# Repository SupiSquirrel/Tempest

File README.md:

# Tempest
Tempest: Etek 5 / GTek / Drone 2 / Clone 5 / Shocker SFT/NXT Paintball Board

This product is open source!

## Hardware
The hardware is released under [Creative Commons ShareAlike 4.0 International](https://creativecommons.org/licenses/by-sa/4.0/).

Please use, reuse, and modify these files as you see fit. Please release anything derivative under the same license.

Distributed as-is; no warranty is given.

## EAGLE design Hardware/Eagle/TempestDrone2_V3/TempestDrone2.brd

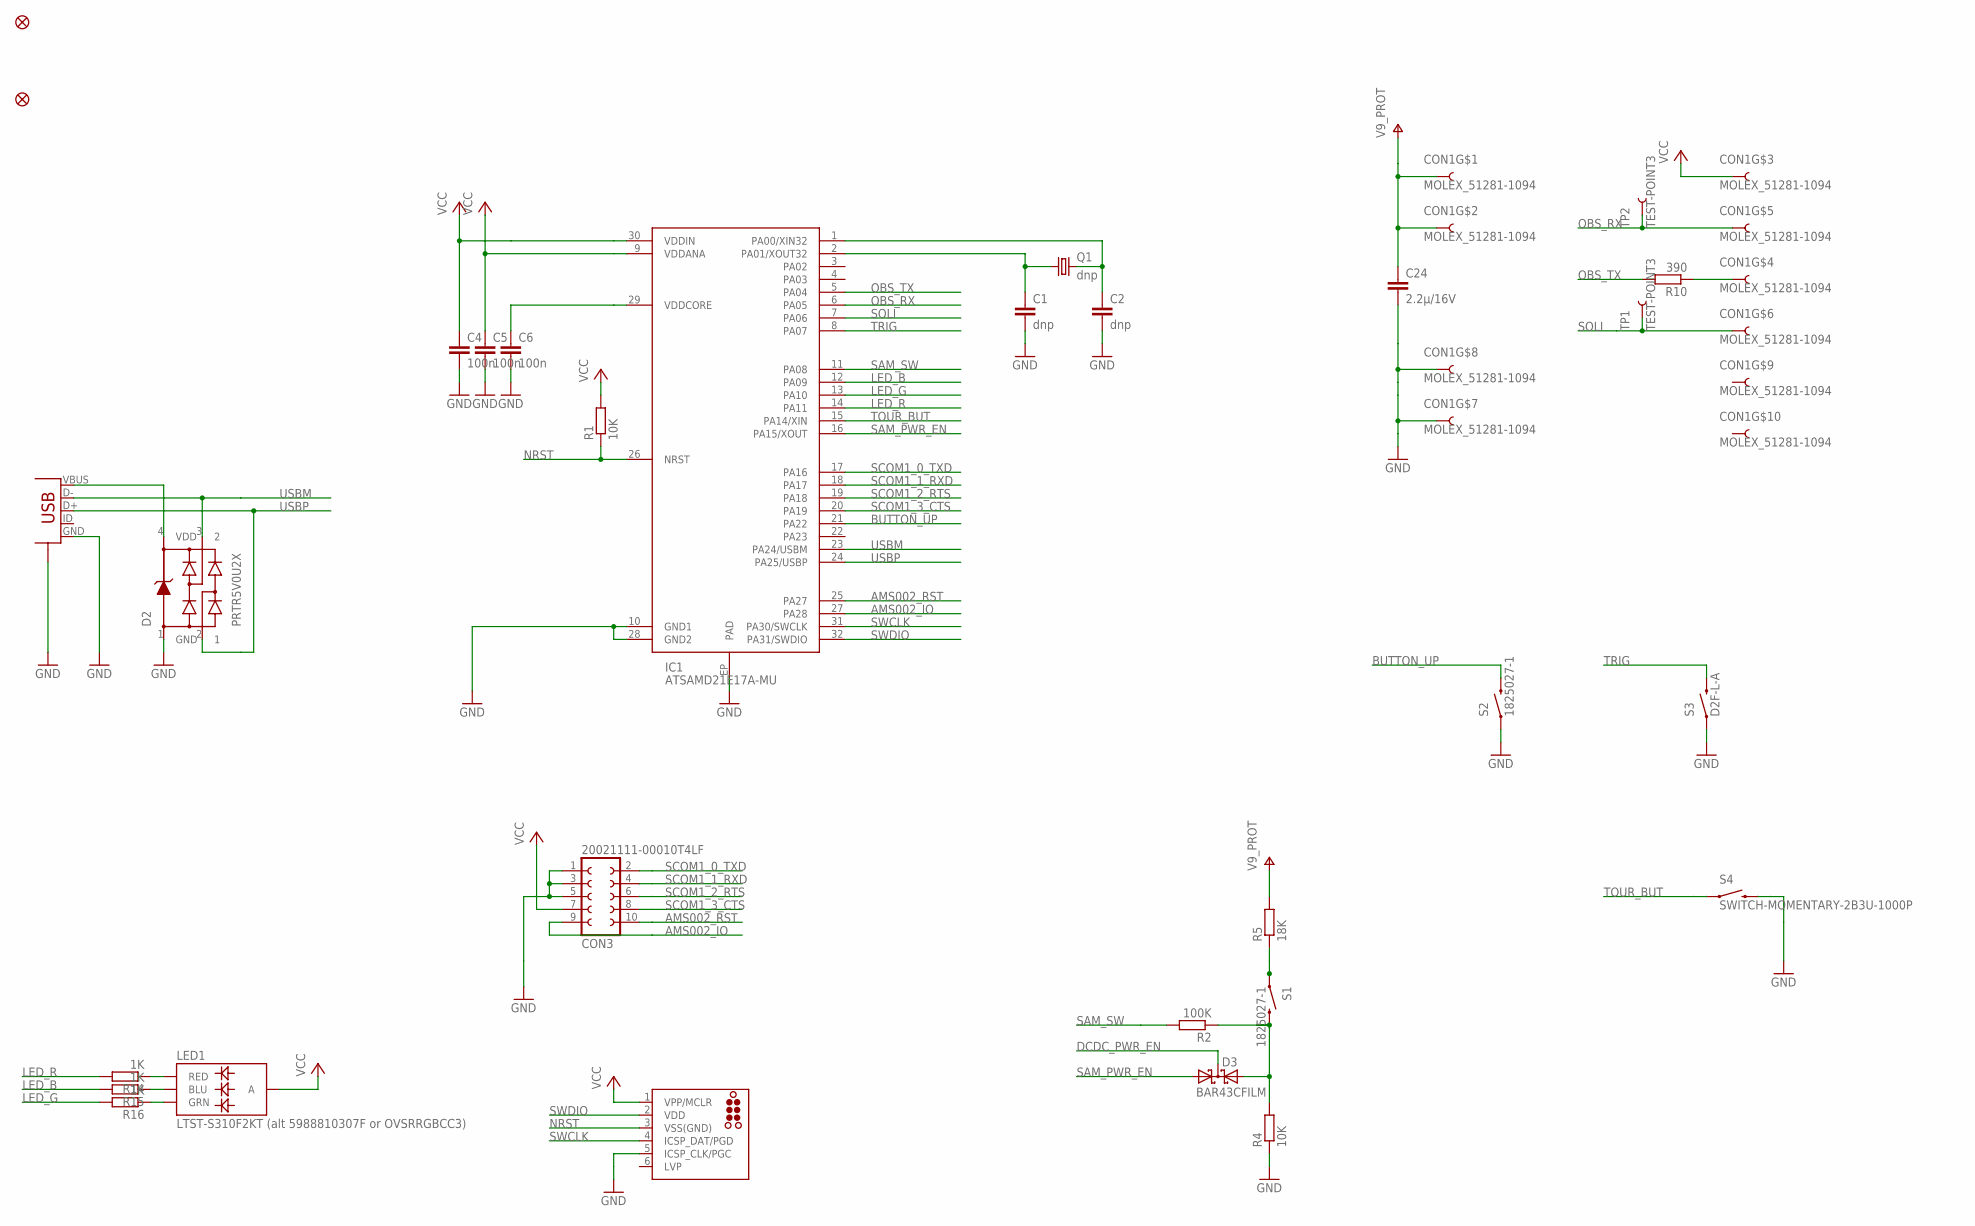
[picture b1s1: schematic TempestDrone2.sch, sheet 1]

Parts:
C1, C2: dnp; _0603MP
C4, C5, C6: 100n; _0603MP
C24: 2.2µ/16V; C0805
CON1: MOLEX_51281-1094; MOLEX_51281; PART# 51281-1094
CON3: 20021111-00010T4LF; FE02-2-HD-2; PART# 20021111-00010T4LF
CON4: USB-MICRO-A; USB-MICROB; PART# ZX62-B-5PA(11)
D2: PRTR5V0U2X; AUTOPILOT_SOT143B; PART# PRTR5V0U2X
D3: BAR43CFILM; SOT23
FID1, FID6: FIDUCIALUFIDUCIAL; MICRO-FIDUCIAL
IC1: ATSAMD21E17A-MU; QFN-32; PART# ATSAMD21E17A-MU
LED1: LTST-S310F2KT (alt 5988810307F or OVSRRGBCC3); RGB-LED-SMD-SIDE; PART# LTST-S310F2KT
Q1: dnp; XTAL_32X15
R1, R4: 10K; _0603MP
R2: 100K; _0603MP
R5: 18K; _0603MP
R10: 390; _0603MP
R14, R15, R16: 1K; _0603MP
S1, S2: 1825027-1; TACTILE-PTH-SIDEEZ; PART# 1-1825027-1
S3: D2F-L-A; D2F-A; PART# D2F-L-A
S4: SWITCH-MOMENTARY-2B3U-1000P; PUSHBUTTON-MICRO3; PART# B3U-1000P
TC2030-CTX-NL: dnp; TC2030-MCP-NL
TP1, TP2: TEST-POINT3; PAD.03X.03

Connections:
AMS002_IO: CON3.9, IC1.27 (PA28)
AMS002_RST: CON3.10, IC1.25 (PA27)
BUTTON_UP: IC1.21 (PA22), S2.2
DCDC_PWR_EN: D3.3 (CC); also elsewhere on the board
GND: C1.2, C2.2, C4.2, C5.2, C6.2, C24.2, CON1.7, CON1.8, CON3.1, CON3.3, CON3.5, CON4.GND, CON4.GND@1 (GND), CON4.GND@2 (GND), CON4.GND@3 (GND), CON4.GND@4 (GND), CON4.GND@5 (GND), CON4.GND@6 (GND), D2.1 (GND), IC1.10 (GND1), IC1.28 (GND2), IC1.EP (PAD), R4.1, S2.1, S3.COM (1), S4.2A (2), TC2030-CTX-NL.5 (ICSP_CLK/PGC); also elsewhere on the board
LED_B: IC1.12 (PA09), R15.2
LED_G: IC1.13 (PA10), R16.2
LED_R: IC1.14 (PA11), R14.2
unnamed: C2.1, IC1.1 (PA00/XIN32), Q1.2
unnamed: C6.1, IC1.29 (VDDCORE)
unnamed: C1.1, IC1.2 (PA01/XOUT32), Q1.1
unnamed: CON4.VBUS, D2.4 (VDD)
unnamed: D3.2 (A2), R2.1, R4.2, S1.2
unnamed: CON1.4, R10.1
unnamed: R5.1, S1.1
unnamed: LED1.1 (RED), R14.1
unnamed: LED1.3 (BLU), R15.1
unnamed: LED1.2 (GRN), R16.1
NRST: IC1.26 (NRST), R1.1, TC2030-CTX-NL.3 (VSS(GND))
OBS_RX: CON1.5, IC1.6 (PA05), TP2.P$1
OBS_TX: IC1.5 (PA04), R10.2
SAM_PWR_EN: D3.1 (A1), IC1.16 (PA15/XOUT)
SAM_SW: IC1.11 (PA08), R2.2
SCOM1_0_TXD: CON3.2, IC1.17 (PA16)
SCOM1_1_RXD: CON3.4, IC1.18 (PA17)
SCOM1_2_RTS: CON3.6, IC1.19 (PA18)
SCOM1_3_CTS: CON3.8, IC1.20 (PA19)
SOLI: CON1.6, IC1.7 (PA06), TP1.P$1
SWCLK: IC1.31 (PA30/SWCLK), TC2030-CTX-NL.4 (ICSP_DAT/PGD)
SWDIO: IC1.32 (PA31/SWDIO), TC2030-CTX-NL.2 (VDD)
TOUR_BUT: IC1.15 (PA14/XIN), S4.1A (1)
TRIG: IC1.8 (PA07), S3.NO (2)
USBM: CON4.D-, D2.3 (2), IC1.23 (PA24/USBM)
USBP: CON4.D+, D2.2 (1), IC1.24 (PA25/USBP)
V9_PROT: C24.1, CON1.1, CON1.2, R5.2; also elsewhere on the board
VCC: C4.1, C5.1, CON1.3, CON3.7, IC1.9 (VDDANA), IC1.30 (VDDIN), LED1.4 (A), R1.2, TC2030-CTX-NL.1 (VPP/MCLR); also elsewhere on the board

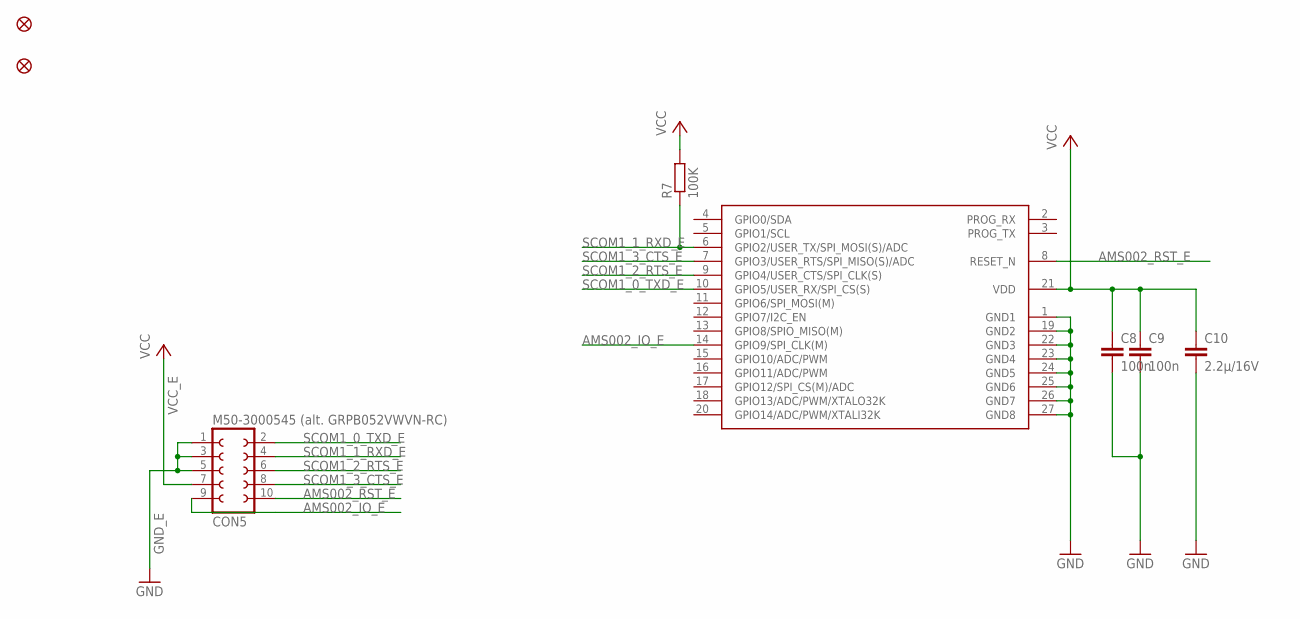
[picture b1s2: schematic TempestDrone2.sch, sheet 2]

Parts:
C8, C9: 100n; _0603MP
C10: 2.2µ/16V; C0805
CON5: M50-3000545 (alt. GRPB052VWVN-RC); FE02-2-HD-2; PART# M50-3000545
FID3, FID5: FIDUCIALUFIDUCIAL; MICRO-FIDUCIAL
R7: 100K; _0603MP
U$1: AMS001/AMS002; AMS00X; PART# AMS001 or AMS002

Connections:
AMS002_IO_E: CON5.9, U$1.14 (GPIO9/SPI_CLK(M))
AMS002_RST_E: CON5.10, U$1.8 (RESET_N)
GND_E: C8.2, C9.2, C10.2, CON5.1, CON5.3, CON5.5, U$1.1 (GND1), U$1.19 (GND2), U$1.22 (GND3), U$1.23 (GND4), U$1.24 (GND5), U$1.25 (GND6), U$1.26 (GND7), U$1.27 (GND8)
SCOM1_0_TXD_E: CON5.2, U$1.10 (GPIO5/USER_RX/SPI_CS(S))
SCOM1_1_RXD_E: CON5.4, R7.1, U$1.6 (GPIO2/USER_TX/SPI_MOSI(S)/ADC)
SCOM1_2_RTS_E: CON5.6, U$1.9 (GPIO4/USER_CTS/SPI_CLK(S))
SCOM1_3_CTS_E: CON5.8, U$1.7 (GPIO3/USER_RTS/SPI_MISO(S)/ADC)
VCC_E: C8.1, C9.1, C10.1, CON5.7, R7.2, U$1.21 (VDD)

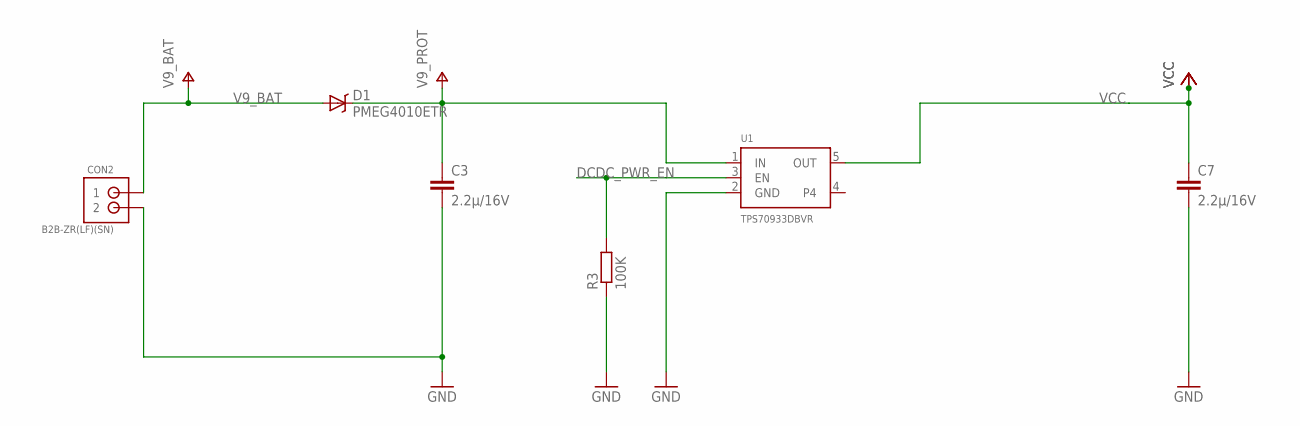
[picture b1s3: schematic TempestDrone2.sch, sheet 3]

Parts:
C3, C7: 2.2µ/16V; C0805
CON2: B2B-ZR(LF)(SN); S2B-ZR; PART# B2B-ZR(LF)(SN)
D1: PMEG4010ETR; SOD123
R3: 100K; _0603MP
U1: TPS70933DBVR; SOT23-5; PART# TPS70933DBVR

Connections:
DCDC_PWR_EN: R3.2, U1.3 (EN); also elsewhere on the board
GND: C3.2, C7.2, CON2.2, R3.1, U1.2 (GND); also elsewhere on the board
V9_BAT: CON2.1, D1.A
V9_PROT: C3.1, D1.C, U1.1 (IN); also elsewhere on the board
VCC: C7.1, U1.5 (OUT); also elsewhere on the board

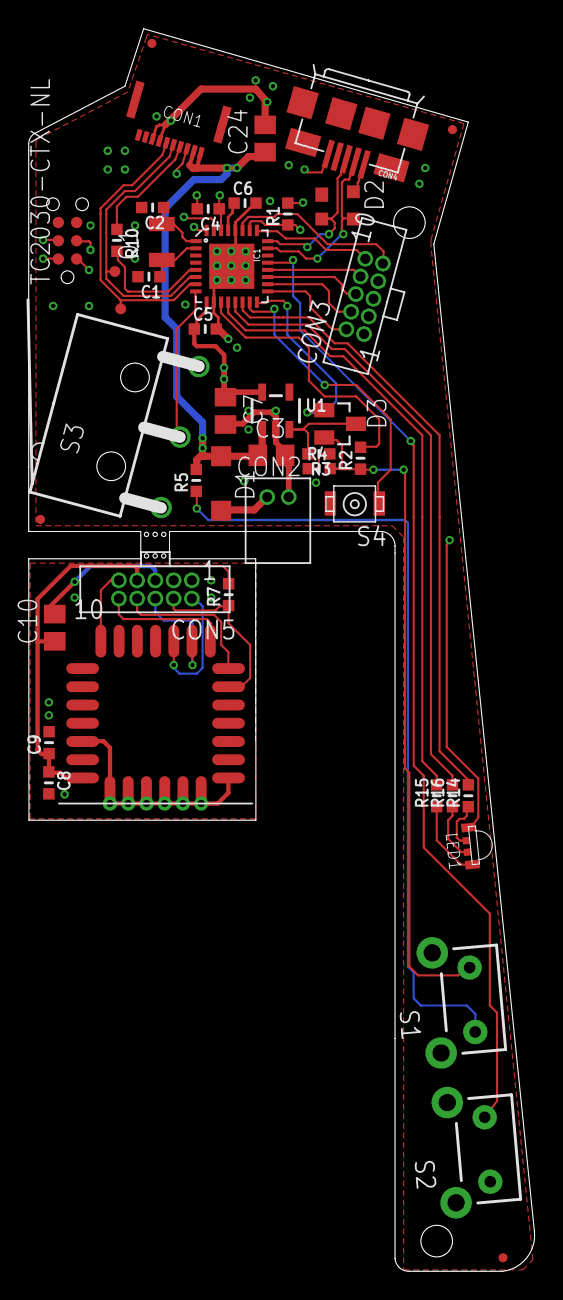
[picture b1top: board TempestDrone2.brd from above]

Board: 4 copper layers, 35.2 x 86.5 mm, 45 parts (0 on the bottom side), 45 nets.

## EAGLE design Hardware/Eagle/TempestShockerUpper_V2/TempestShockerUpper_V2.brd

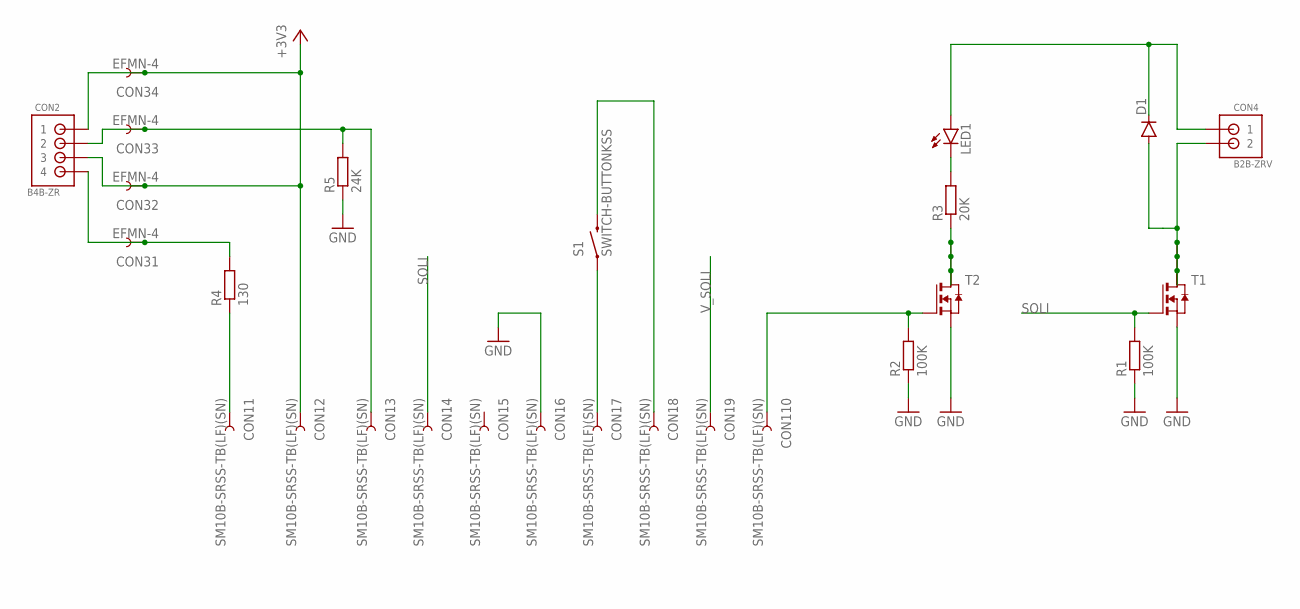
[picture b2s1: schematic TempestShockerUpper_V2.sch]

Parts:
CON1: SM10B-SRSS-TB(LF)(SN); SM10B-SRSS-TB
CON2: B4B-ZR; S4B-ZR
CON3: EFMN-4
CON4: B2B-ZRV; S2B-ZR-VERT
D1: DIODE-SSOD123; SOD-123
LED1: LED0603; LED-0603
R1, R2: 100K; _0603MP
R3: 20K; _0603MP
R4: 130; _0603MP
R5: 24K; _0603MP
S1: SWITCH-BUTTONKSS; KSS
T1, T2: NMOSSOT23-6; SOT23-6

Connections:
+3V3: CON1.2, CON2.1, CON2.3, CON3.2, CON3.4
GND: CON1.6, R1.1, R2.1, R5.1, T1.4 (S), T2.4 (S)
unnamed: CON2.4, CON3.1, R4.2
unnamed: CON1.1, R4.1
unnamed: CON1.3, CON2.2, CON3.3, R5.2
unnamed: CON1.10, R2.2, T2.3 (G)
unnamed: CON1.7, S1.1
unnamed: CON1.8, S1.2
unnamed: LED1.C, R3.2
unnamed: R3.1, T2.1 (D), T2.2 (D1), T2.5 (D2), T2.6 (D3)
unnamed: CON4.2, D1.A, T1.1 (D), T1.2 (D1), T1.5 (D2), T1.6 (D3)
SOLI: CON1.4, R1.2, T1.3 (G)
V_SOLI: CON1.9, CON4.1, D1.C, LED1.A

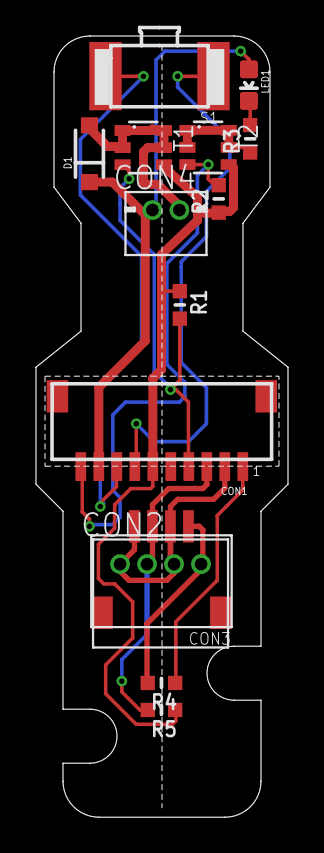
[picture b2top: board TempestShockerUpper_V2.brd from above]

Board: 2 copper layers, 14.0 x 43.4 mm, 15 parts (0 on the bottom side), 13 nets.

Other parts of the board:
U$2: SHOCKER-OUTLINE-UPPER-SHORT

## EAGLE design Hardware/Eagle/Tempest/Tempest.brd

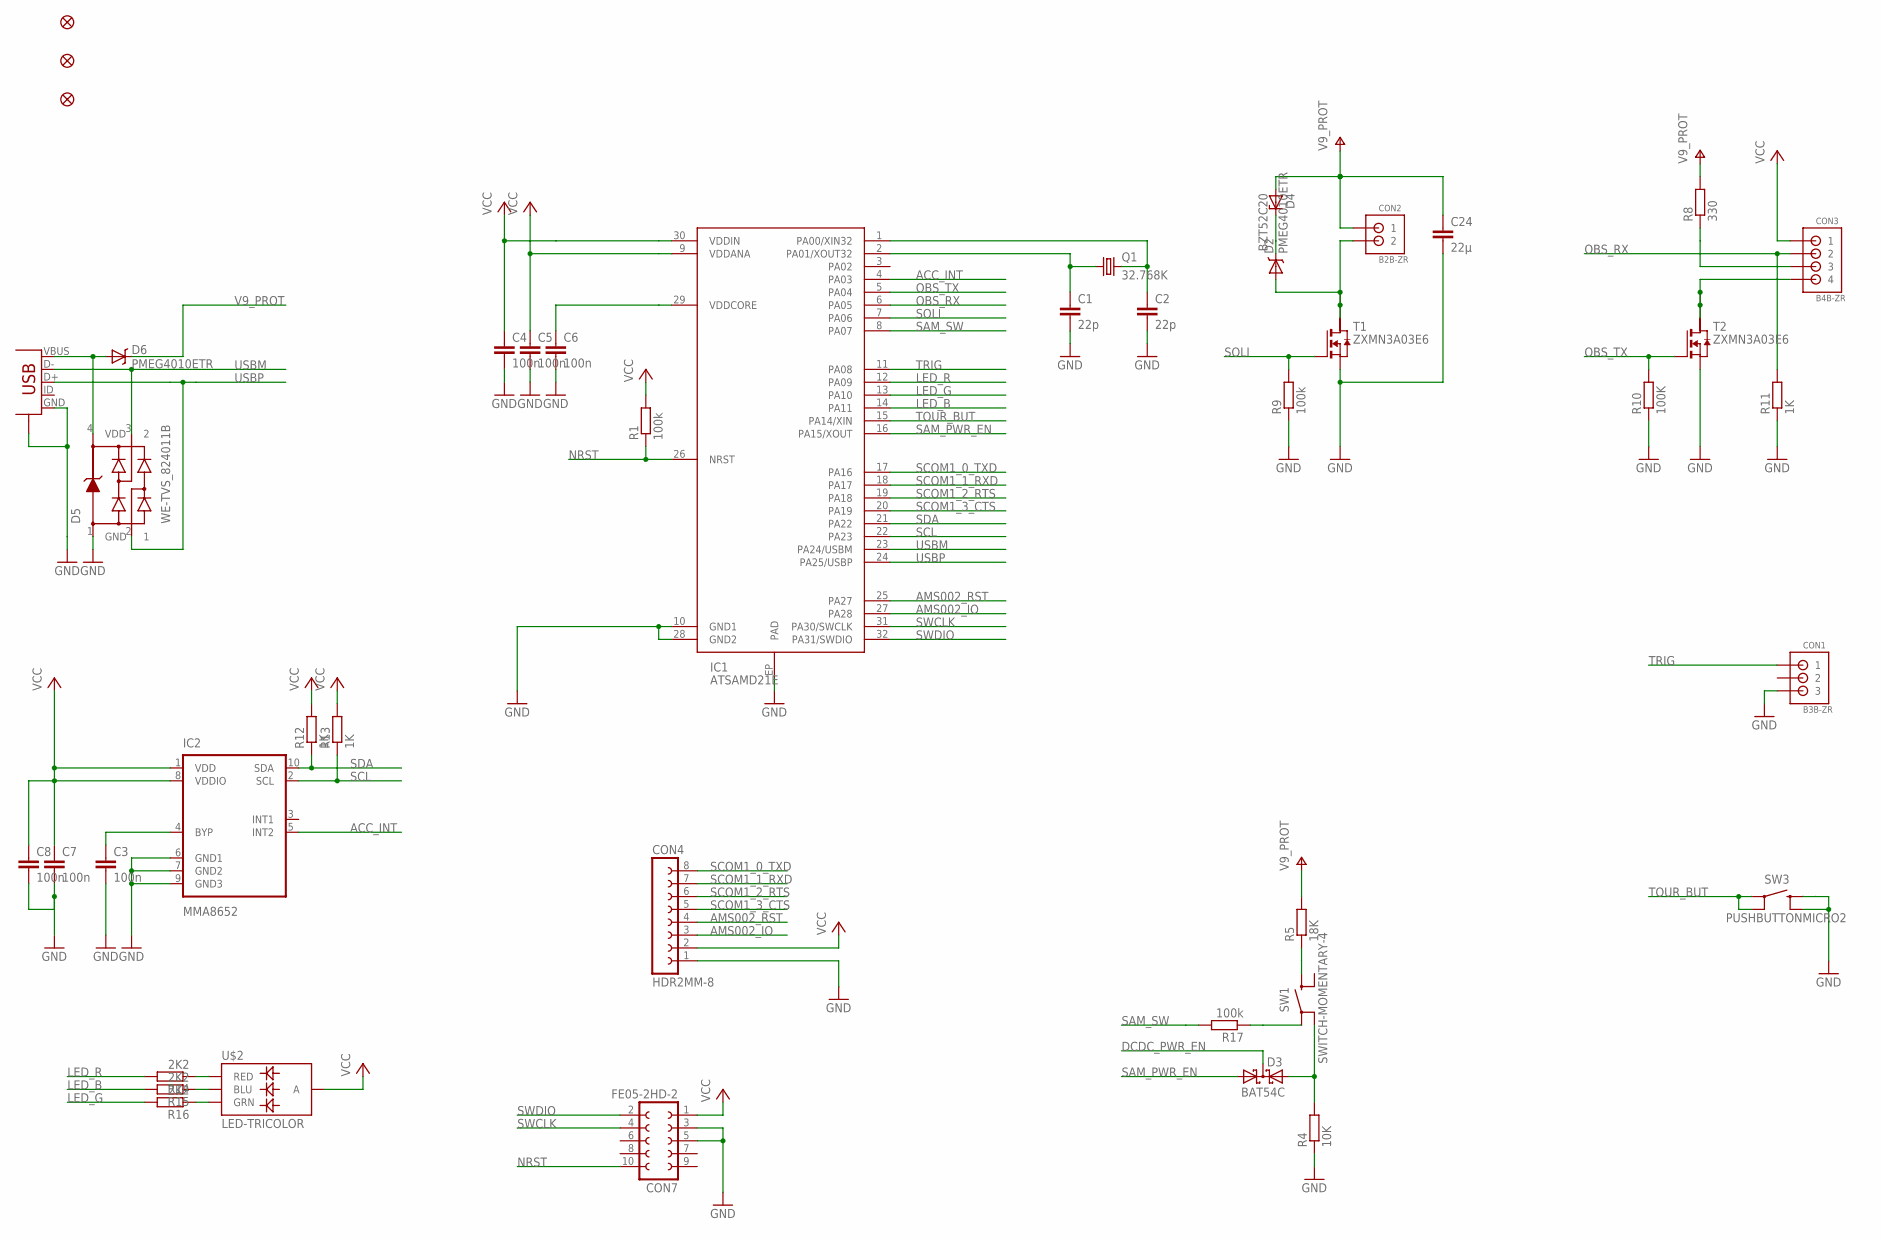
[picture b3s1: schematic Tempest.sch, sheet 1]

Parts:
C1, C2: 22p; _0603MP
C3, C4, C5, C6, C7, C8: 100n; _0603MP
C24: 22µ; C1206
CON1: B3B-ZR; S3B-ZR
CON2: B2B-ZR; S2B-ZR
CON3: B4B-ZR; S4B-ZR
CON4: HDR2MM-8
CON6: USB-MICRO-A; USB-MICROB
CON7: FE05-2HD-2; FE02-2-HD-2
D2, D6: PMEG4010ETR; SOD123
D3: BAT54C; SOT23
D4: BZT52C20; SOD123
D5: WE-TVS_824011B; AUTOPILOT_SOT143B
FID1, FID2, FID6: FIDUCIALUFIDUCIAL; MICRO-FIDUCIAL
IC1: ATSAMD21E; QFN-32
IC2: MMA8652; DFN-10
Q1: 32.768K; XTAL_32X15
R1, R9, R17: 100k; _0603MP
R4: 10K; _0603MP
R5: 18K; _0603MP
R8: 330; R0805
R10: 100K; _0603MP
R11, R12, R13: 1K; _0603MP
R14, R15, R16: 2K2; _0603MP
SW1: SWITCH-MOMENTARY-4; TACTILE_SWITCH_TALL
SW3: PUSHBUTTONMICRO2; PUSHBUTTON-MICRO2
T1, T2: ZXMN3A03E6; SOT23-6
U$2: LED-TRICOLOR; LED-TRICOLOR-SMD

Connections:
ACC_INT: IC1.4 (PA03), IC2.5 (INT2)
AMS002_IO: CON4.3, IC1.27 (PA28)
AMS002_RST: CON4.4, IC1.25 (PA27)
DCDC_PWR_EN: D3.3 (CC); also elsewhere on the board
GND: C1.2, C2.2, C3.2, C4.2, C5.2, C6.2, C7.2, C8.2, C24.2, CON1.3, CON4.1, CON6.GND, CON6.GND@1 (GND), CON6.GND@2 (GND), CON6.GND@3 (GND), CON6.GND@4 (GND), CON6.GND@5 (GND), CON6.GND@6 (GND), CON7.3, CON7.5, D5.1 (GND), IC1.10 (GND1), IC1.28 (GND2), IC1.EP (PAD), IC2.6 (GND1), IC2.7 (GND2), IC2.9 (GND3), R4.1, R9.1, R10.1, R11.1, SW3.2A (2), SW3.2B (2A), T1.4 (S), T2.4 (S); also elsewhere on the board
LED_B: IC1.14 (PA11), R15.2
LED_G: IC1.13 (PA10), R16.2
LED_R: IC1.12 (PA09), R14.2
unnamed: C2.1, IC1.1 (PA00/XIN32), Q1.2
unnamed: C6.1, IC1.29 (VDDCORE)
unnamed: C1.1, IC1.2 (PA01/XOUT32), Q1.1
unnamed: D3.2 (A2), R4.2, SW1.A2 (1A)
unnamed: CON2.2, D2.A, T1.1 (D), T1.2 (D1), T1.6 (D3)
unnamed: R5.1, SW1.B1 (2)
unnamed: R17.1, SW1.A1 (1)
unnamed: C3.1, IC2.4 (BYP)
unnamed: CON3.4, T2.1 (D), T2.2 (D1), T2.6 (D3)
unnamed: CON3.3, R8.1
unnamed: D2.C, D4.C
unnamed: CON6.VBUS, D5.4 (VDD), D6.A
unnamed: R14.1, U$2.2 (RED)
unnamed: R15.1, U$2.3 (BLU)
unnamed: R16.1, U$2.4 (GRN)
NRST: CON7.10, IC1.26 (NRST), R1.1
OBS_RX: CON3.2, IC1.6 (PA05), R11.2
OBS_TX: IC1.5 (PA04), R10.2, T2.3 (G)
SAM_PWR_EN: D3.1 (A1), IC1.16 (PA15/XOUT)
SAM_SW: IC1.8 (PA07), R17.2
SCL: IC1.22 (PA23), IC2.2 (SCL), R13.1
SCOM1_0_TXD: CON4.8, IC1.17 (PA16)
SCOM1_1_RXD: CON4.7, IC1.18 (PA17)
SCOM1_2_RTS: CON4.6, IC1.19 (PA18)
SCOM1_3_CTS: CON4.5, IC1.20 (PA19)
SDA: IC1.21 (PA22), IC2.10 (SDA), R12.1
SOLI: IC1.7 (PA06), R9.2, T1.3 (G)
SWCLK: CON7.4, IC1.31 (PA30/SWCLK)
SWDIO: CON7.2, IC1.32 (PA31/SWDIO)
TOUR_BUT: IC1.15 (PA14/XIN), SW3.1A (1), SW3.1B (1A)
TRIG: CON1.1, IC1.11 (PA08)
USBM: CON6.D-, D5.3 (2), IC1.23 (PA24/USBM)
USBP: CON6.D+, D5.2 (1), IC1.24 (PA25/USBP)
V9_PROT: C24.1, CON2.1, D4.A, D6.C, R5.2, R8.2; also elsewhere on the board
VCC: C4.1, C5.1, C7.1, C8.1, CON3.1, CON4.2, CON7.1, IC1.9 (VDDANA), IC1.30 (VDDIN), IC2.1 (VDD), IC2.8 (VDDIO), R1.2, R12.2, R13.2, U$2.1 (A); also elsewhere on the board

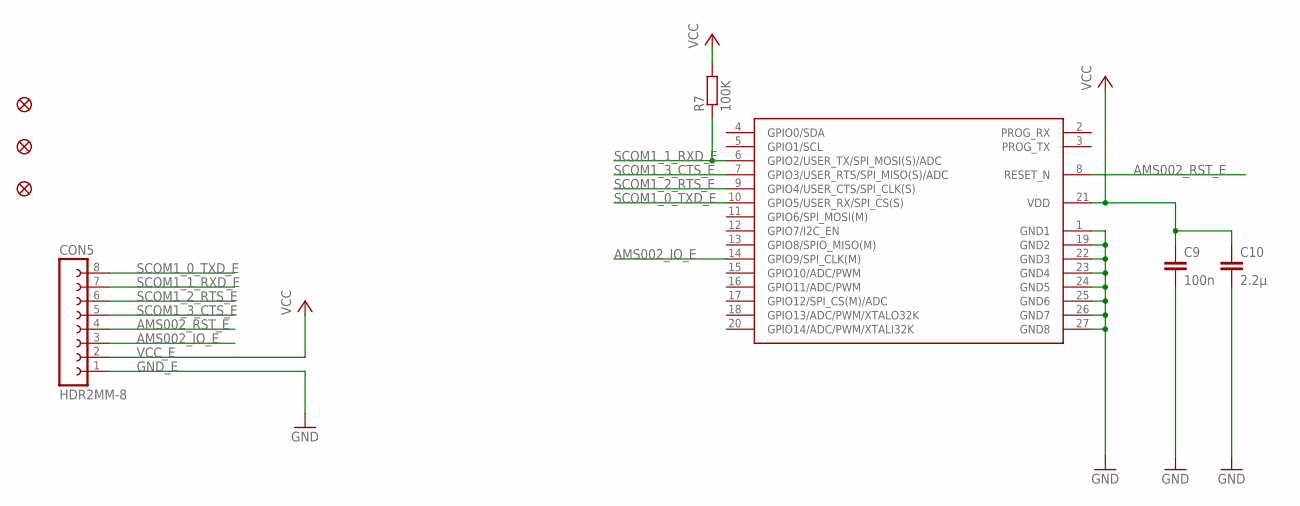
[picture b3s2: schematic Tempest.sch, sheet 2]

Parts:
C9: 100n; _0603MP
C10: 2.2µ; _0603MP
CON5: HDR2MM-8
FID3, FID4, FID5: FIDUCIALUFIDUCIAL; MICRO-FIDUCIAL
R7: 100K; _0603MP
U$1: AMS002; AMS00X

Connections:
AMS002_IO_E: CON5.3, U$1.14 (GPIO9/SPI_CLK(M))
AMS002_RST_E: CON5.4, U$1.8 (RESET_N)
GND_E: C9.2, C10.2, CON5.1, U$1.1 (GND1), U$1.19 (GND2), U$1.22 (GND3), U$1.23 (GND4), U$1.24 (GND5), U$1.25 (GND6), U$1.26 (GND7), U$1.27 (GND8)
SCOM1_0_TXD_E: CON5.8, U$1.10 (GPIO5/USER_RX/SPI_CS(S))
SCOM1_1_RXD_E: CON5.7, R7.1, U$1.6 (GPIO2/USER_TX/SPI_MOSI(S)/ADC)
SCOM1_2_RTS_E: CON5.6, U$1.9 (GPIO4/USER_CTS/SPI_CLK(S))
SCOM1_3_CTS_E: CON5.5, U$1.7 (GPIO3/USER_RTS/SPI_MISO(S)/ADC)
VCC_E: C9.1, C10.1, CON5.2, R7.2, U$1.21 (VDD)

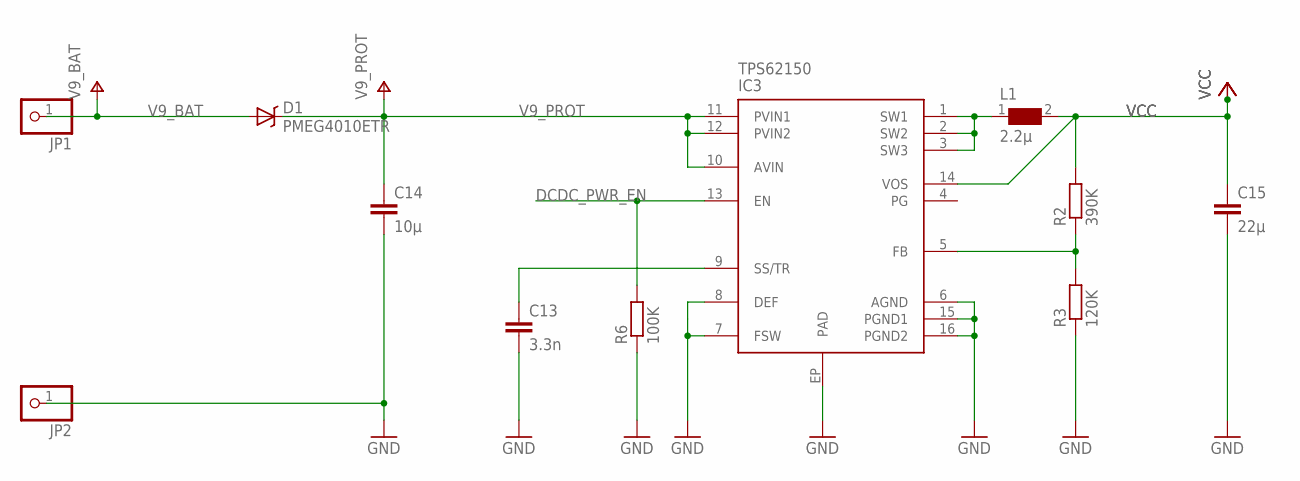
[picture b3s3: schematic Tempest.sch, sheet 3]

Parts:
C13: 3.3n; _0603MP
C14: 10µ; C1206
C15: 22µ; C1206
D1: PMEG4010ETR; SOD123
IC3: TPS62150; QFN-16
JP1, JP2: PINHD-1X1; 1X01
L1: 2.2µ; WE-TPC_2828
R2: 390K; _0603MP
R3: 120K; _0603MP
R6: 100K; _0603MP

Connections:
DCDC_PWR_EN: IC3.13 (EN), R6.2; also elsewhere on the board
GND: C13.2, C14.2, C15.2, IC3.6 (AGND), IC3.7 (FSW), IC3.8 (DEF), IC3.15 (PGND1), IC3.16 (PGND2), IC3.EP (PAD), JP2.1, R3.1, R6.1; also elsewhere on the board
unnamed: C13.1, IC3.9 (SS/TR)
unnamed: IC3.1 (SW1), IC3.2 (SW2), IC3.3 (SW3), L1.1
unnamed: IC3.5 (FB), R2.1, R3.2
V9_BAT: D1.A, JP1.1
V9_PROT: C14.1, D1.C, IC3.10 (AVIN), IC3.11 (PVIN1), IC3.12 (PVIN2); also elsewhere on the board
VCC: C15.1, IC3.14 (VOS), L1.2, R2.2; also elsewhere on the board

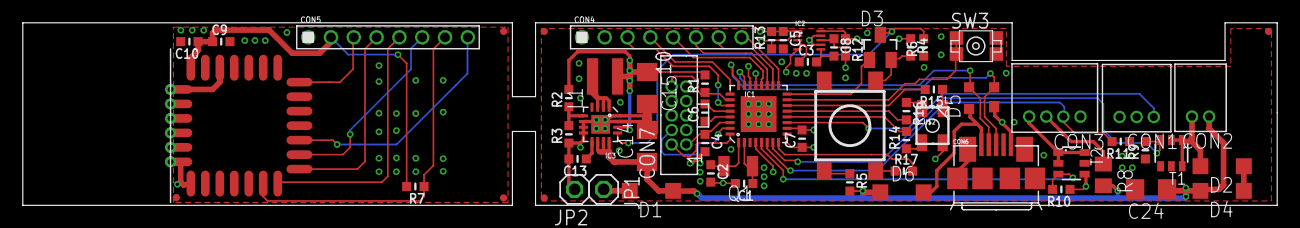
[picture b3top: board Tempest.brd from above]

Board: 4 copper layers, 110.0 x 16.0 mm, 63 parts (0 on the bottom side), 55 nets.

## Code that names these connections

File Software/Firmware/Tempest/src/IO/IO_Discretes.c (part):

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	
		// red led
		pin_conf.direction  = PORT_PIN_DIR_OUTPUT;
		port_pin_set_config(PIN_PA09, &pin_conf);
		port_pin_set_output_level(PIN_PA09, true);
	
		//green led
		pin_conf.direction  = PORT_PIN_DIR_OUTPUT;
		port_pin_set_config(PIN_PA10, &pin_conf);
		port_pin_set_output_level(PIN_PA10, true);
	
		// blue led
		pin_conf.direction  = PORT_PIN_DIR_OUTPUT;
		port_pin_set_config(PIN_PA11, &pin_conf);
		port_pin_set_output_level(PIN_PA11, true);
	
		// ams00x reset
		pin_conf.direction  = PORT_PIN_DIR_OUTPUT;
		port_pin_set_config(PIN_PA27, &pin_conf);
		port_pin_set_output_level(PIN_PA27, true);
	
		// ams00x mode_sel
		pin_conf.direction  = PORT_PIN_DIR_OUTPUT;
		port_pin_set_config(PIN_PA28, &pin_conf);
		port_pin_set_output_level(PIN_PA28, false);
	
		// solenoid
		// handled by pwm
		// 	pin_conf.direction  = PORT_PIN_DIR_OUTPUT;
		// 	port_pin_set_config(PIN_PA06, &pin_conf);
		// 	port_pin_set_output_level(PIN_PA06, false);	
	
		// obs tx
		// handled by pwm
		// 	pin_conf.direction  = PORT_PIN_DIR_OUTPUT;
		// 	port_pin_set_config(PIN_PA04, &pin_conf);
		// 	port_pin_set_output_level(PIN_PA04, false);	
	
		// power enable
		pin_conf.direction  = PORT_PIN_DIR_OUTPUT;
		port_pin_set_config(PIN_PA15, &pin_conf);
		port_pin_set_output_level(PIN_PA15, false);
	
		// debug
		pin_conf.direction  = PORT_PIN_DIR_OUTPUT;
		port_pin_set_config(PIN_PA18, &pin_conf);
		port_pin_set_output_level(PIN_PA18, false);		
	
	
		// ------------ inputs
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		// ams00x status_led
		pin_conf.direction  = PORT_PIN_DIR_INPUT;
		pin_conf.input_pull = PORT_PIN_PULL_UP;
		port_pin_set_config(PIN_PA19, &pin_conf);	
	
		// tournament button
		pin_conf.direction  = PORT_PIN_DIR_INPUT;
		pin_conf.input_pull = PORT_PIN_PULL_UP;
		port_pin_set_config(PIN_PA14, &pin_conf);
	
		// trigger button
		pin_conf.direction  = PORT_PIN_DIR_INPUT;
		pin_conf.input_pull = PORT_PIN_PULL_UP;
		port_pin_set_config(PIN_PA08, &pin_conf);
	
		// main button
		pin_conf.direction  = PORT_PIN_DIR_INPUT;
		pin_conf.input_pull = PORT_PIN_PULL_NONE;
		port_pin_set_config(PIN_PA07, &pin_conf);
	
#endif
	
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	
		// red led
		pin_conf.direction  = PORT_PIN_DIR_OUTPUT;
		port_pin_set_config(PIN_PA09, &pin_conf);
		port_pin_set_output_level(PIN_PA09, true);
		system_pinmux_pin_set_output_strength(PIN_PA09, SYSTEM_PINMUX_PIN_STRENGTH_HIGH);
	
		//green led
		pin_conf.direction  = PORT_PIN_DIR_OUTPUT;
		port_pin_set_config(PIN_PA10, &pin_conf);
		port_pin_set_output_level(PIN_PA10, true);
		system_pinmux_pin_set_output_strength(PIN_PA10, SYSTEM_PINMUX_PIN_STRENGTH_HIGH);
	
		// blue led
		pin_conf.direction  = PORT_PIN_DIR_OUTPUT;
		port_pin_set_config(PIN_PA11, &pin_conf);
		port_pin_set_output_level(PIN_PA11, true);
		system_pinmux_pin_set_output_strength(PIN_PA11, SYSTEM_PINMUX_PIN_STRENGTH_HIGH);
	
		// ams00x reset
		pin_conf.direction  = PORT_PIN_DIR_OUTPUT;
		port_pin_set_config(PIN_PA27, &pin_conf);
		port_pin_set_output_level(PIN_PA27, true);
	
		// ams00x mode_sel
		pin_conf.direction  = PORT_PIN_DIR_OUTPUT;
		port_pin_set_config(PIN_PA28, &pin_conf);
		port_pin_set_output_level(PIN_PA28, false);
	
		// power enable
		pin_conf.direction  = PORT_PIN_DIR_OUTPUT;
		port_pin_set_config(PIN_PA15, &pin_conf);
		port_pin_set_output_level(PIN_PA15, false);
	
		// debug
		pin_conf.direction  = PORT_PIN_DIR_OUTPUT;
		port_pin_set_config(PIN_PA18, &pin_conf);
		port_pin_set_output_level(PIN_PA18, false);
		
		// obs tx
		// handled by gpio
		pin_conf.direction  = PORT_PIN_DIR_OUTPUT;
		port_pin_set_config(PIN_PA04, &pin_conf);
		port_pin_set_output_level(PIN_PA04, true);
		system_pinmux_pin_set_output_strength(PIN_PA04, SYSTEM_PINMUX_PIN_STRENGTH_HIGH);
	
	
		// ------------ inputs
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		// ams00x status_led input
		pin_conf.direction  = PORT_PIN_DIR_INPUT;
		pin_conf.input_pull = PORT_PIN_PULL_UP;
		port_pin_set_config(PIN_PA19, &pin_conf);
	
		// tournament button
		pin_conf.direction  = PORT_PIN_DIR_INPUT;
		pin_conf.input_pull = PORT_PIN_PULL_UP;
		port_pin_set_config(PIN_PA14, &pin_conf);
	
		// trigger button
		pin_conf.direction  = PORT_PIN_DIR_INPUT;
		pin_conf.input_pull = PORT_PIN_PULL_UP;
		port_pin_set_config(PIN_PA07, &pin_conf);
	
		// main button
		pin_conf.direction  = PORT_PIN_DIR_INPUT;
		pin_conf.input_pull = PORT_PIN_PULL_NONE;
		port_pin_set_config(PIN_PA08, &pin_conf);
		
		// up button
		pin_conf.direction  = PORT_PIN_DIR_INPUT;
		pin_conf.input_pull = PORT_PIN_PULL_UP;
		port_pin_set_config(PIN_PA22, &pin_conf);
		
		// obs rx
		pin_conf.direction  = PORT_PIN_DIR_INPUT;
		pin_conf.input_pull = PORT_PIN_PULL_UP;
		port_pin_set_config(PIN_PA05, &pin_conf);		
	
#endif

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
		// red led
		pin_conf.direction  = PORT_PIN_DIR_OUTPUT;
		port_pin_set_config(PIN_PA09, &pin_conf);
		port_pin_set_output_level(PIN_PA09, true);
		system_pinmux_pin_set_output_strength(PIN_PA09, SYSTEM_PINMUX_PIN_STRENGTH_HIGH);

		//green led
		pin_conf.direction  = PORT_PIN_DIR_OUTPUT;
		port_pin_set_config(PIN_PA10, &pin_conf);
		port_pin_set_output_level(PIN_PA10, true);
		system_pinmux_pin_set_output_strength(PIN_PA10, SYSTEM_PINMUX_PIN_STRENGTH_HIGH);

		// blue led
		pin_conf.direction  = PORT_PIN_DIR_OUTPUT;
		port_pin_set_config(PIN_PA11, &pin_conf);
		port_pin_set_output_level(PIN_PA11, true);
		system_pinmux_pin_set_output_strength(PIN_PA11, SYSTEM_PINMUX_PIN_STRENGTH_HIGH);

		// ams00x reset
		pin_conf.direction  = PORT_PIN_DIR_OUTPUT;
		port_pin_set_config(PIN_PA22, &pin_conf);
		port_pin_set_output_level(PIN_PA22, true);

		// ams00x mode_sel
		pin_conf.direction  = PORT_PIN_DIR_OUTPUT;
		port_pin_set_config(PIN_PA23, &pin_conf);
		port_pin_set_output_level(PIN_PA23, false);

		// power enable
		pin_conf.direction  = PORT_PIN_DIR_OUTPUT;
		port_pin_set_config(PIN_PA03, &pin_conf);
		port_pin_set_output_level(PIN_PA03, false);

		// debug
		pin_conf.direction  = PORT_PIN_DIR_OUTPUT;
		port_pin_set_config(PIN_PA18, &pin_conf);
		port_pin_set_output_level(PIN_PA18, false);

		// obs tx
		// handled by gpio
		pin_conf.direction  = PORT_PIN_DIR_OUTPUT;
		port_pin_set_config(PIN_PA04, &pin_conf);
		port_pin_set_output_level(PIN_PA04, true);
		system_pinmux_pin_set_output_strength(PIN_PA04, SYSTEM_PINMUX_PIN_STRENGTH_HIGH);
		
		// power led
		pin_conf.direction  = PORT_PIN_DIR_OUTPUT;
		port_pin_set_config(PIN_PA00, &pin_conf);
		port_pin_set_output_level(PIN_PA00, false);
		system_pinmux_pin_set_output_strength(PIN_PA00, SYSTEM_PINMUX_PIN_STRENGTH_HIGH);
		


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		// ams00x status_led input
		pin_conf.direction  = PORT_PIN_DIR_INPUT;
		pin_conf.input_pull = PORT_PIN_PULL_UP;
		port_pin_set_config(PIN_PA19, &pin_conf);

		// tournament button
		pin_conf.direction  = PORT_PIN_DIR_INPUT;
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		// trigger button
		pin_conf.direction  = PORT_PIN_DIR_INPUT;
		pin_conf.input_pull = PORT_PIN_PULL_UP;
		port_pin_set_config(PIN_PA07, &pin_conf);

		// main button
		pin_conf.direction  = PORT_PIN_DIR_INPUT;
		pin_conf.input_pull = PORT_PIN_PULL_NONE;
		port_pin_set_config(PIN_PA08, &pin_conf);

		// up button
		//pin_conf.direction  = PORT_PIN_DIR_INPUT;
		//pin_conf.input_pull = PORT_PIN_PULL_UP;
		//port_pin_set_config(PIN_PA22, &pin_conf);

		// obs rx
		pin_conf.direction  = PORT_PIN_DIR_INPUT;
		pin_conf.input_pull = PORT_PIN_PULL_NONE;
		port_pin_set_config(PIN_PA05, &pin_conf);

#endif
	
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		
#ifdef ETEK5
		case IO_DISCRETES_CHANNEL_TRIGGER:
				return (!port_pin_get_input_level(PIN_PA08));
				break;
		case IO_DISCRETES_CHANNEL_AMS_STATUSLED:
				return (port_pin_get_input_level(PIN_PA19));
				break;
		case IO_DISCRETES_CHANNEL_TOURNAMENT_SWITCH:
				return (!port_pin_get_input_level(PIN_PA14));
				break;
		case IO_DISCRETES_CHANNEL_MAIN_SWITCH:
				return (port_pin_get_input_level(PIN_PA07));
				break;	
		case IO_DISCRETES_CHANNEL_OBS_RX:
				return (port_pin_get_input_level(PIN_PA05));
				break;											
				
#endif

#ifdef DRONE2
		case IO_DISCRETES_CHANNEL_TRIGGER:
				return (!port_pin_get_input_level(PIN_PA07));
				break;
		case IO_DISCRETES_CHANNEL_AMS_STATUSLED:
				return (port_pin_get_input_level(PIN_PA19));
				break;
		case IO_DISCRETES_CHANNEL_TOURNAMENT_SWITCH:
				return (!port_pin_get_input_level(PIN_PA14));
				break;
		case IO_DISCRETES_CHANNEL_MAIN_SWITCH:
				return (port_pin_get_input_level(PIN_PA08));
				break;
		case IO_DISCRETES_CHANNEL_OBS_RX:
				return (port_pin_get_input_level(PIN_PA05));
				break;
		case IO_DISCRETES_CHANNEL_UP_SWITCH:
				return (!port_pin_get_input_level(PIN_PA22));
				break;				
		
#endif

#ifdef SHOCKER
		case IO_DISCRETES_CHANNEL_TRIGGER:
				return (!port_pin_get_input_level(PIN_PA07));
				break;
		case IO_DISCRETES_CHANNEL_AMS_STATUSLED:
				return (port_pin_get_input_level(PIN_PA19));
				break;
		case IO_DISCRETES_CHANNEL_TOURNAMENT_SWITCH:
				return (!port_pin_get_input_level(PIN_PA02));
				break;
		case IO_DISCRETES_CHANNEL_MAIN_SWITCH:
				return (port_pin_get_input_level(PIN_PA08));
				break;
// 		case IO_DISCRETES_CHANNEL_OBS_RX:
// 				return (port_pin_get_input_level(PIN_PA05));
// 				break;
// 		case IO_DISCRETES_CHANNEL_UP_SWITCH:
// 				return (!port_pin_get_input_level(PIN_PA22));
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
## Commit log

2015-04-02 CommitTest
2015-04-02 Test
2015-04-06 Initial hardware.
2015-05-26 - Hardware license information added
2015-05-26 - Link to CC added
2015-05-26 - Firmware initial commit.
2015-10-12 -Drone 2 target added. -Eyes activated
2015-10-12 -Drone 2 version added.
2015-10-25 -Migrated to Atmel Studio 7 -Minor improvements/bugfixes
2016-01-27 - Minor fixes. - USB added - TAG connect added
2016-02-03 - Minor improvements
2016-02-26 - Eye on/off - Defaults
2016-03-06 - Added 100K between power button and controller - Added part # for fets and diodes
2016-03-28 - Shocker SFT/NXT Draft
2016-03-28 - Basic lib
2016-05-06 - New Shocker upper board for Luxe solenoid - Update of lib
2016-05-06 - Shocker variant
2016-05-06 - Alpha/Prelim Android App

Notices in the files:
Software/Firmware/Tempest/src/IO/IO_Discretes.c:
Copyright (C) 2015 Matthias Friedrich
Tempest Firmware is free software: you can redistribute it and/or modify
it under the terms of the GNU Lesser General Public License as published by
the Free Software Foundation, either version 3 of the License, or
(at your option) any later version.
parts and their libraries:
squirrel: ©2009 ROFA.cz - modified and updated by Robert Darlington ‹rdarlington@gmail.com›
SparkFun-Passives: Licensing: Creative Commons ShareAlike 4.0 International - https://creativecommons.org/licenses/by-sa/4.0
